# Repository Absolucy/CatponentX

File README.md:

# CatponentX

This is a board that, in theory, allows for high quality component video output from the original Xbox. It replaces the AV Port, with a PCB that sticks out the back, providing high-quality analog video and digital audio output.

## Installation Instructions

These have only been tested on Xbox 1.0! Pads may differ on later Xbox revisions. 
Although, they should be the same on 1.1, but I believe 1.2-1.4 and 1.6 have different encoders, and likely a different board layout in that area.

### Y/Pb/Pr wires

(need an image)
1. Remove the inductors at L4A2, L4A3, and L4A3. They are above the video encoder, near the AV port. They're black and blue, and very big. Should be easy to remove with low-melt solder.
2. Solder 3 wires to the *bottom* pads (the one facing the video encoder chip). They should be long enough to go out the AV port. I personally used [this 3-core shielded wire](https://amazon.com/gp/product/B01LNH8POQ), to reduce interference.
3. Solder those wires to the Y/Pb/Pr pads on the CatponentX chip. I honestly forgot which one was which, so uh, if someone could figure that out, that'd be great.

### AV Port wires

You will need to solder 3 wires (5V, GND, and S/PDIF) to the A/V port holes here. They go to the appropiately labeled pads on the CatponentX PCB. Shielding is not needed.

You will also need to solder two jumpers between the Mode 2/Mode 3 holes, and the adjacent ground points. (Technically, ground is ground and it doesn't matter which ground you use, but it's just convienent to use the adjacent ground pins)

5V = Red  
GND = Black  
Green = S/PDIF  
Mode 2 = Dark Blue (solder to ground)  
Mode 3 = Light Blue (solder to ground)  

## Bill of Materials

| **References** | **Part Description**              | **Quanity** | **Price (Total)** | **Digi-Key**                                                                                                         |
| -------------- | --------------------------------- | ----------- | ----------------- | -------------------------------------------------------------------------------------------------------------------- |
| C1             | 10uF 16V Aluminum Capacitor       | 1           | $0.56             | [493-3913-1-ND](https://www.digikey.com/en/products/detail/nichicon/UCL1C100MCL1GS/2300262)                          |
| C2, C3         | 0.1uF 100V Ceramic Capacitor      | 1           | $0.20             | [1276-6840-1-ND](https://www.digikey.com/en/products/detail/samsung-electro-mechanics/CL21B104KCFNNNE/5961324)       |
| R1, R2, R3     | 75 Ohm 1/8W 0805 Resistor         | 3           | $0.30             | [CR0805-FX-75R0ELFCT-ND](https://www.digikey.com/en/products/detail/bourns-inc/CR0805-FX-75R0ELF/3740954)            |
| R4             | 160 Ohm 1/8W 0805 Resistor        | 1           | $0.10             | [118-CR0805-FX-1600ELFCT-ND](https://www.digikey.com/en/products/detail/bourns-inc/CR0805-FX-1600ELF/3784671)        |
| LED1           | Diffused Red 2V LED               | 1           | $0.39             | [754-1901-ND](https://www.digikey.com/en/products/detail/kingbright/WP914IDT)                                        |
| FILTER1        | THS7316DR Analog Video Filter/Amp | 1           | $1.01             | [296-26684-1-ND](https://www.digikey.com/en/products/detail/texas-instruments/THS7316DR/1905373)                     |
| RCA1           | 3 Component RCA Jacks             | 1           | $2.56             | [SC1854-ND](https://www.digikey.com/en/products/detail/switchcraft-inc/PJRAN3X1U03X/1288816)                         |
| TOSLINK1       | Optical S/PDIF Transmitter        | 1           | N/A               | [3185-FCR684208T-ND](https://www.digikey.com/en/products/detail/cliff-electronic-components-ltd/FCR684208T/15283099) |

**Note**: R4 and LED1 are optional if you don't want a power LED.

## Known Issues

- Video seems too bright (@Absolucy)
- S/PDIF output doesn't work for me (@Absolucy)

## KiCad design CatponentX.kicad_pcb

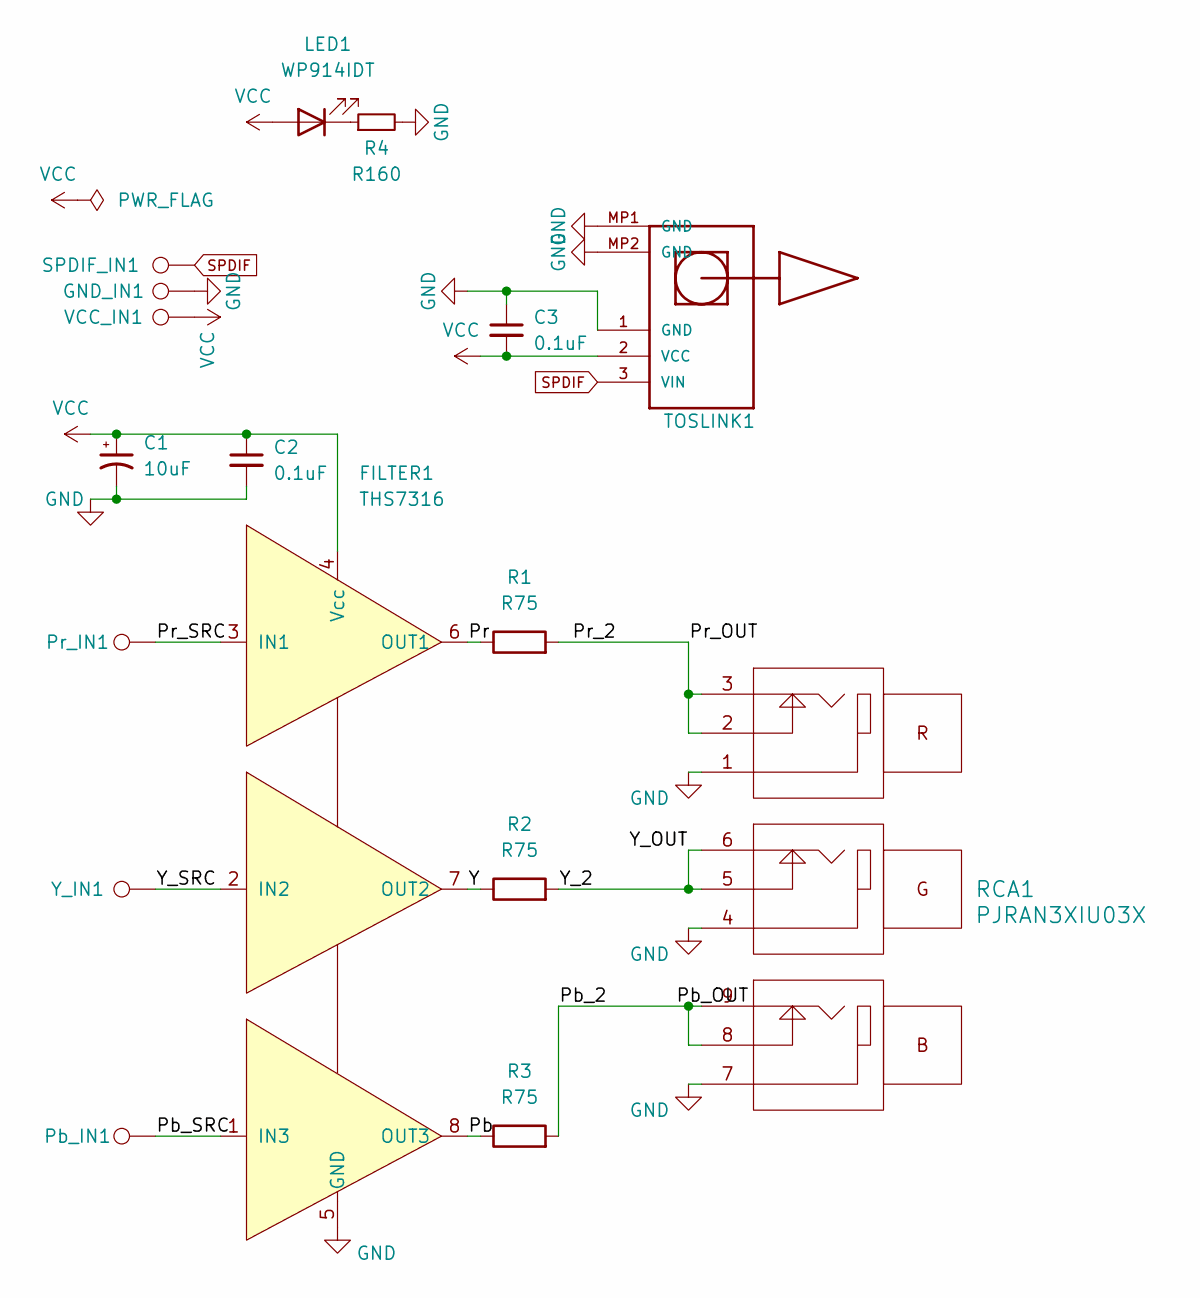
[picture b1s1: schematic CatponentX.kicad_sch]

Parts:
C1: 10uF; CP_Elec_5x5.8; Manufacturer Part Number UCL1C100MCL1GS; Digi-Key Part Number 493-3913-1-ND
C2, C3: 0.1uF; C_0805_2012Metric_Pad1.18x1.45mm_HandSolder; Manufacturer Part Number CL21B104KCFNNNE; Digi-Key Part Number 1276-6840-1-ND
FILTER1: THS7316; Manufacturer Part Number THS7316DR; Digi-Key Part Number 296-26684-1-ND
GND_IN1: Y_IN; TestPoint_Pad_D2.5mm
LED1: WP914IDT; LED_D3.0mm; Manufacturer Part Number WP914IDT; Digi-Key Part Number 754-1901-ND
Pb_IN1: Pr_IN; TestPoint_Pad_D2.5mm
Pr_IN1: Y_IN; TestPoint_Pad_D2.5mm
R1, R2, R3: R75; R_0805_2012Metric_Pad1.20x1.40mm_HandSolder; Manufacturer Part Number CR0805-FX-75R0ELF; Digi-Key Part Number CR0805-FX-75R0ELFCT-ND
R4: R160; R_0805_2012Metric_Pad1.20x1.40mm_HandSolder; Manufacturer Part Number CR0805-FX-1600ELF; Digi-Key Part Number 118-CR0805-FX-1600ELFCT-ND
RCA1: PJRAN3XIU03X; PJRAN3X1U; Manufacturer Part Number PJRAN3X1U03X; Digi-Key Part Number SC1854-ND
SPDIF_IN1: Y_IN; TestPoint_Pad_D2.5mm
TOSLINK1: FCR684208T; FCR684205T
VCC_IN1: Y_IN; TestPoint_Pad_D2.5mm
Y_IN1: Pb_IN; TestPoint_Pad_D2.5mm

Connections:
/Pb: FILTER1.8 (OUT3), R3.1
/Pb_2: R3.2, RCA1.8, RCA1.9
/Pb_SRC: FILTER1.1 (IN3), Pb_IN1.1
/Pr: FILTER1.6 (OUT1), R1.1
/Pr_2: R1.2, RCA1.2, RCA1.3
/Pr_SRC: FILTER1.3 (IN1), Pr_IN1.1
/Y: FILTER1.7 (OUT2), R2.1
/Y_2: R2.2, RCA1.5, RCA1.6
/Y_SRC: FILTER1.2 (IN2), Y_IN1.1
GND: C1.2, C2.2, C3.1, FILTER1.5 (GND), GND_IN1.1, R4.2, RCA1.1, RCA1.4, RCA1.7, TOSLINK1.1 (GND), TOSLINK1.MP1 (GND), TOSLINK1.MP2 (GND)
unnamed: LED1.1 (K), R4.1
SPDIF: SPDIF_IN1.1, TOSLINK1.3 (VIN)
VCC: C1.1, C2.1, C3.2, FILTER1.4 (Vcc), LED1.2 (A), TOSLINK1.2 (VCC), VCC_IN1.1

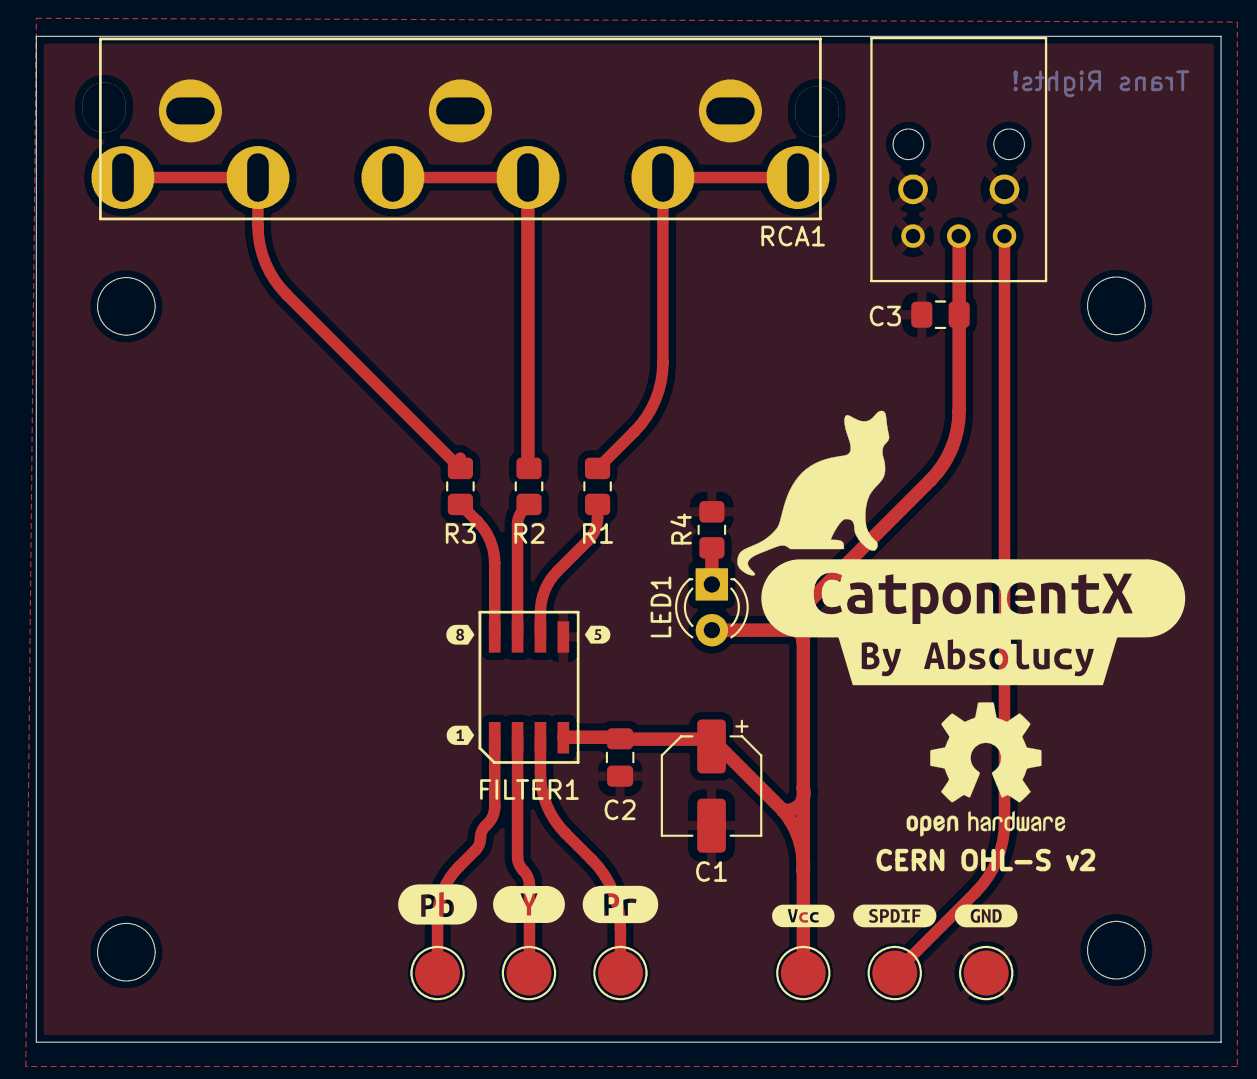
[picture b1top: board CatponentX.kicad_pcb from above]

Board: 2 copper layers, 65.8 x 55.9 mm, 28 parts (0 on the bottom side), 13 nets.

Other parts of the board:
kibuzzard-630BAD88: G***; kibuzzard-630BAD88
kibuzzard-630BAD90: G***; kibuzzard-630BAD90
kibuzzard-630C1A0C: G***; kibuzzard-630C1A0C
kibuzzard-630C1A19: G***; kibuzzard-630C1A19
kibuzzard-630C1A27: G***; kibuzzard-630C1A27
kibuzzard-630D7263: G***; kibuzzard-630D7263
kibuzzard-630D7269: G***; kibuzzard-630D7269
kibuzzard-630E2579: G***; kibuzzard-630E2579
kibuzzard-6303C26E: G***; kibuzzard-6303C26E
kibuzzard-6303C228: G***; kibuzzard-6303C228
kibuzzard-6303C288: G***; kibuzzard-6303C288

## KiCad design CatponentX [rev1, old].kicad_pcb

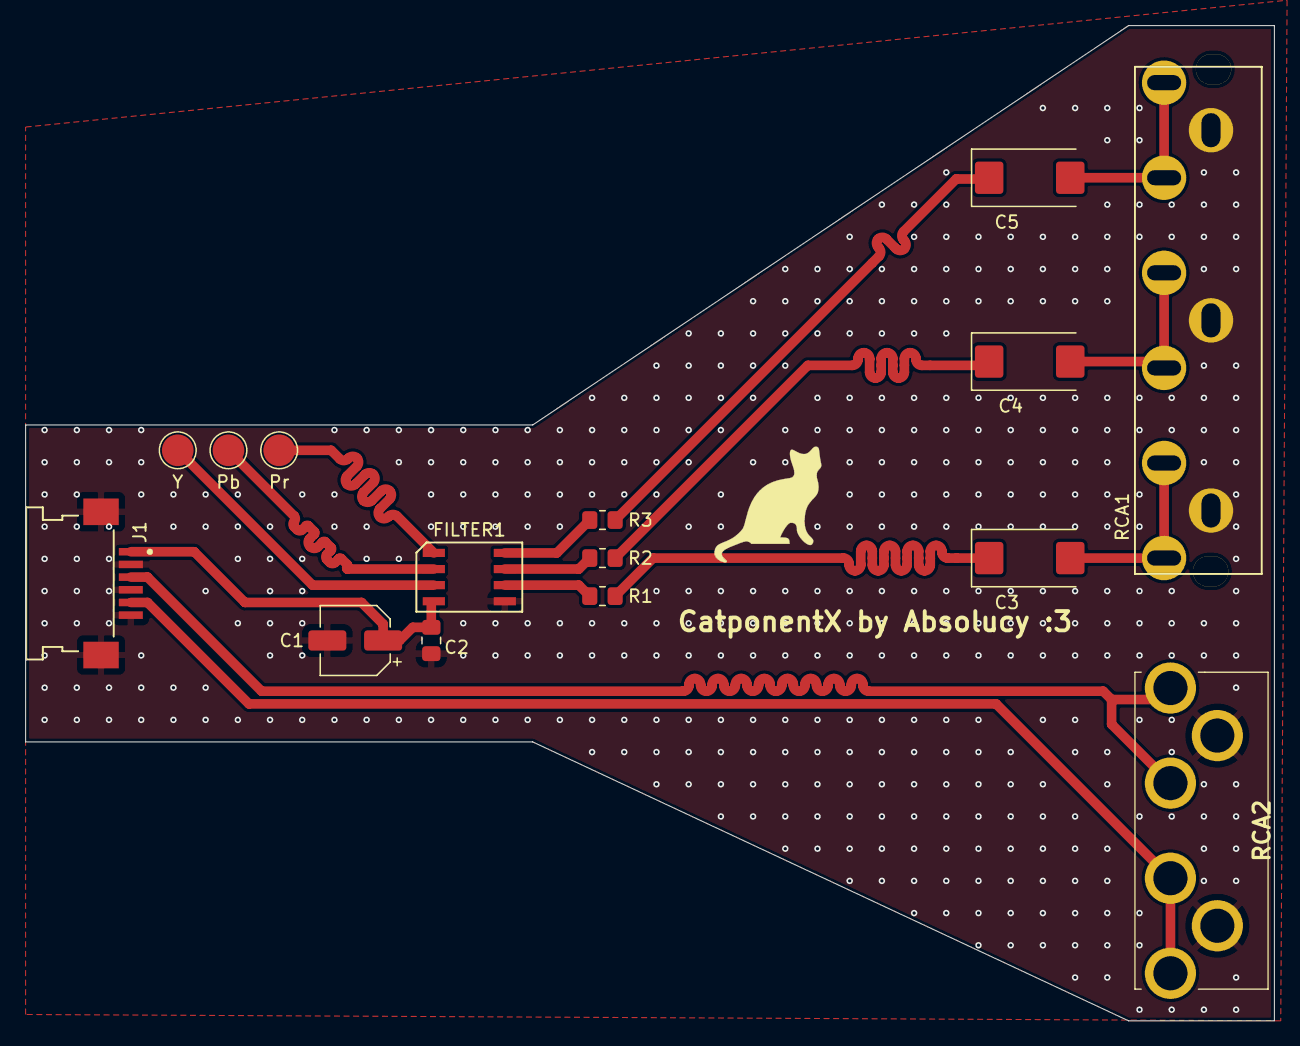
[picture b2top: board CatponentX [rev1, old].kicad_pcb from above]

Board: 2 copper layers, 98.5 x 78.5 mm, 15 parts (0 on the bottom side), 16 nets.

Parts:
C1: 10uF; CP_Elec_5x5.8
C2: 0.1uF; C_0805_2012Metric_Pad1.18x1.45mm_HandSolder
C3, C4, C5: 220uF; CP_EIA-7343-15_Kemet-W_Pad2.25x2.55mm_HandSolder
FILTER1: THS7316
J1: 52207-0660; Molex-52207-0660
Pb: Pb_SRC; TestPoint_Pad_D2.5mm
Pr: Pr_SRC; TestPoint_Pad_D2.5mm
R1, R2, R3: R75; R_0805_2012Metric_Pad1.20x1.40mm_HandSolder
RCA1: PJRAN3XIU03X; PJRAN3X1U
RCA2: PJRAN2X1U01AUX
Y: Y_SRC; TestPoint_Pad_D2.5mm

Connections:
/Pb: FILTER1.7 (OUT2), R2.1
/Pb_2: C4.1, R2.2
/Pb_OUT: C4.2, RCA1.5, RCA1.6
/Pb_SRC: FILTER1.2 (IN2), Pb.1
/Pr: FILTER1.8 (OUT3), R3.1
/Pr_2: C5.1, R3.2
/Pr_OUT: C5.2, RCA1.8, RCA1.9
/Pr_SRC: FILTER1.1 (IN3), Pr.1
/Y: FILTER1.6 (OUT1), R1.1
/Y_2: C3.1, R1.2
/Y_OUT: C3.2, RCA1.2, RCA1.3
/Y_SRC: FILTER1.3 (IN1), Y.1
Audio_L: J1.5, RCA2.2, RCA2.3
Audio_R: J1.3, RCA2.5, RCA2.6
GND: C1.2, C2.2, FILTER1.5 (GND), J1.2, J1.4, J1.6, J1.MP1, J1.MP2, RCA1.1, RCA1.4, RCA1.7, RCA2.1, RCA2.4
VCC: C1.1, C2.1, FILTER1.4 (Vcc), J1.1

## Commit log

2022-10-07 Initial commit: CatponentX

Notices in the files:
CatponentX.kicad_pcb:
CERN OHL-S v2
